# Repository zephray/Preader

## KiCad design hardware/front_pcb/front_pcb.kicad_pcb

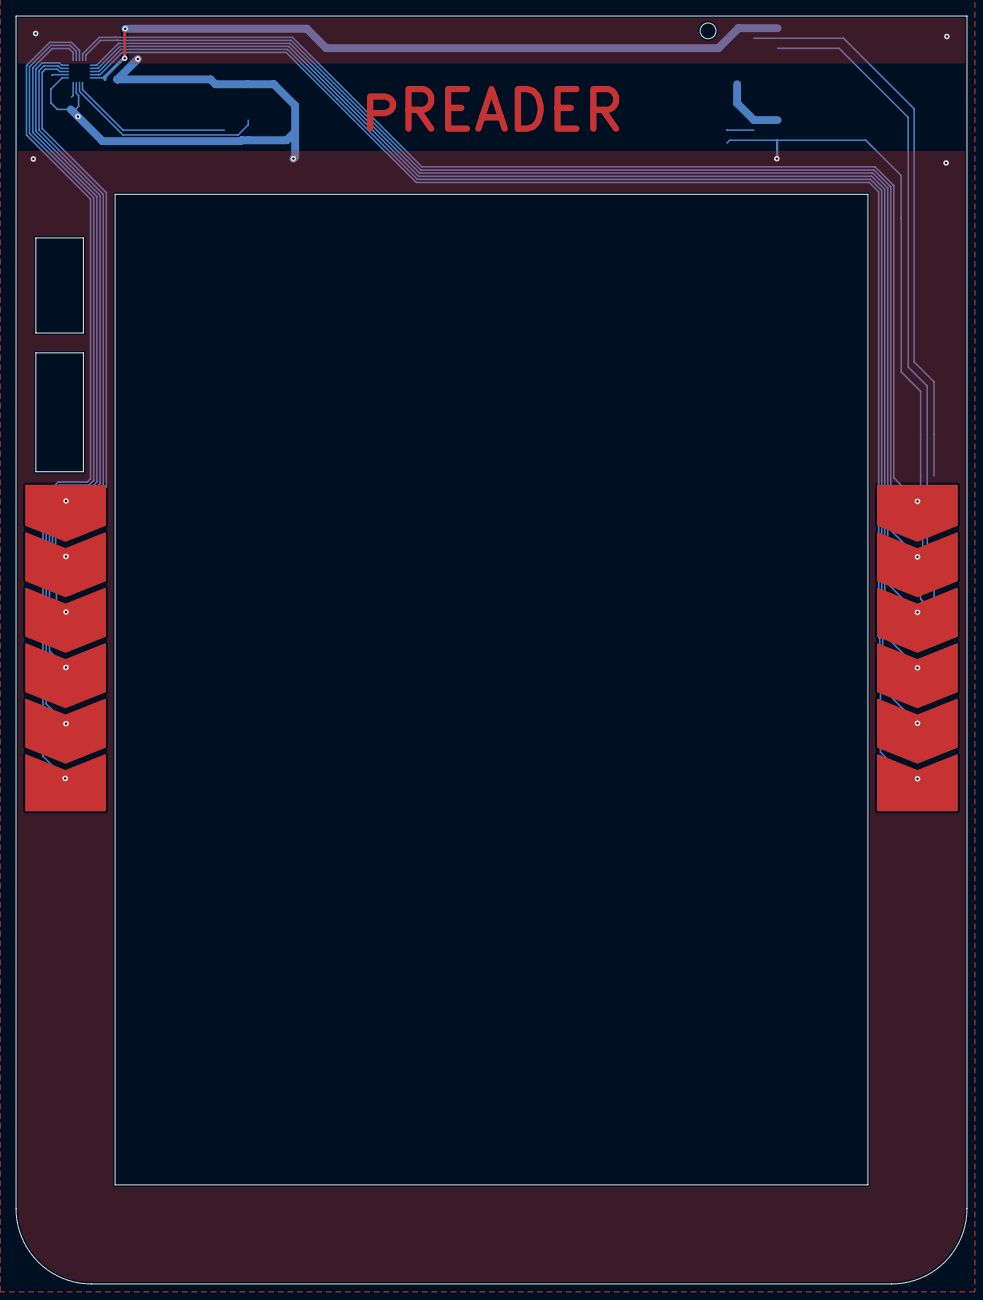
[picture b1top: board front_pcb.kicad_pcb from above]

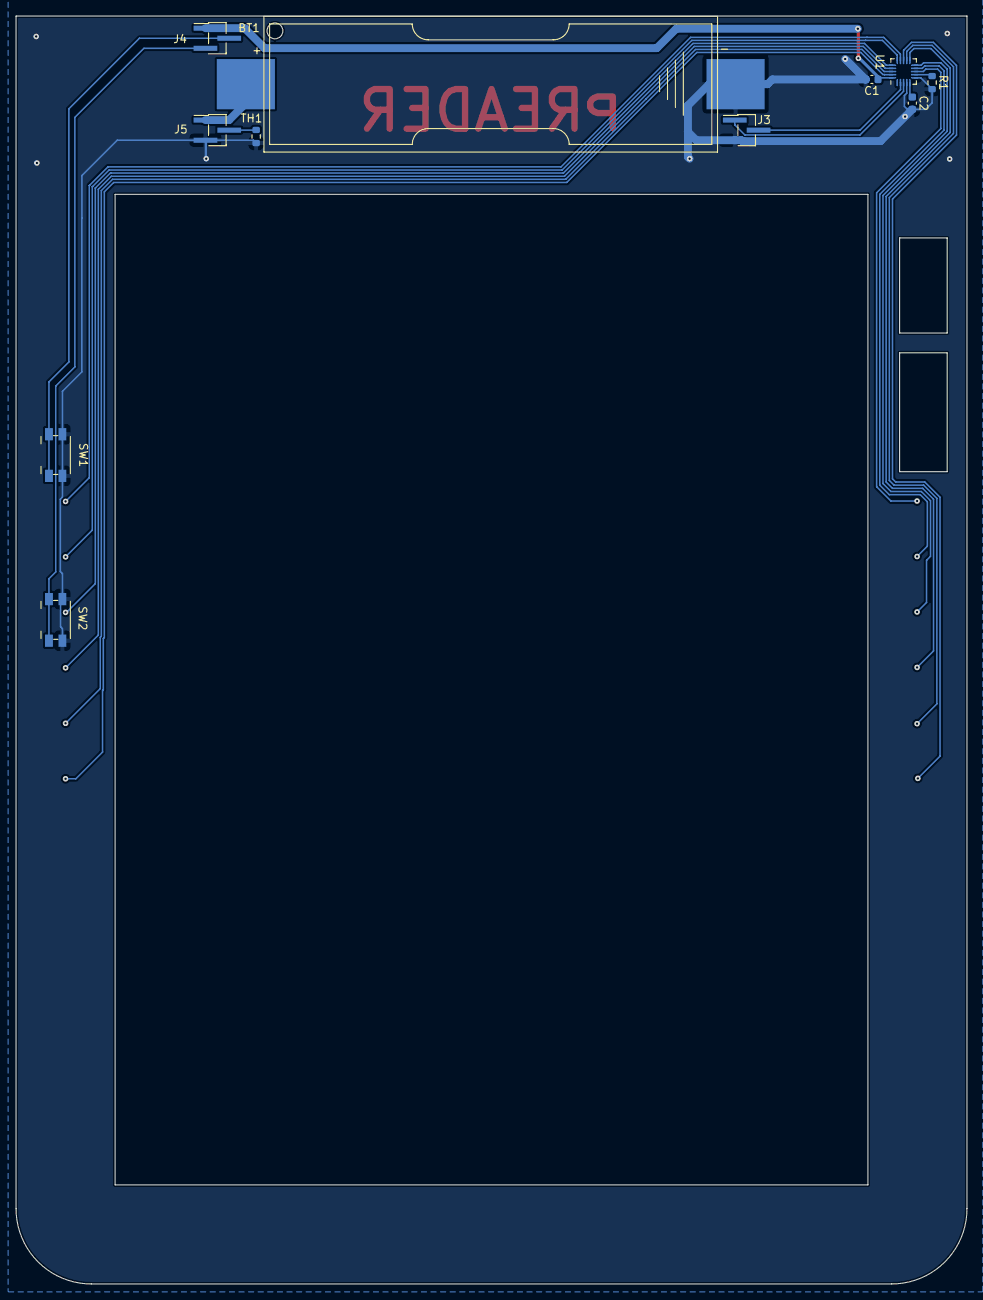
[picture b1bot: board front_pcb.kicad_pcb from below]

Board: 2 copper layers, 120.0 x 160.0 mm, 13 parts (11 on the bottom side), 22 nets.

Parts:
BT1: Keystone_1088_14800; BatteryHolder_Keystone_1088_1xAA
C1, C2: 100nF; C_0603_1608Metric
J1, J2: Conn_01x06; Touch_Sensing_6PADS
J3, J4, J5: Conn_01x03; PinHeader_1x03_P1.27mm_Vertical_SMD_Pin1Left
R1: 75K/1%; R_0603_1608Metric
SW1, SW2: EVQPUJ02K; Panasonic_EVQPUJ_EVQPUA
TH1: Thermistor_NTC; R_0603_1608Metric
U1: MPR121QR2; UQFN-20_3x3mm_P0.4mm

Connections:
+3V3: C1.1, J4.1, U1.20 (VDD)
+BATT: BT1.1 (+), J5.1
/KEY1: J4.2, SW1.1
/KEY2: J4.3, SW2.1
/KP_SCL: J3.1, U1.3 (SDA)
/KP_SDA: J3.2, U1.2 (SCL)
GND: BT1.2 (-), C1.2, C2.2, J3.3, J5.3, R1.2, SW1.2, SW2.2, TH1.2, U1.4 (ADDR), U1.6 (VSS)
unnamed: C2.1, U1.5 (VREG)
unnamed: J1.1, U1.8 (ELE0)
unnamed: J1.2, U1.9 (ELE1)
unnamed: J1.3, U1.10 (ELE2)
unnamed: J1.4, U1.11 (ELE3)
unnamed: J1.5, U1.12 (LED0/ELE4)
unnamed: J1.6, U1.13 (LED1/ELE5)
unnamed: J2.1, U1.14 (LED2/ELE6)
unnamed: J2.2, U1.15 (LED3/ELE7)
unnamed: J2.3, U1.16 (LED4/ELE8)
unnamed: J2.4, U1.17 (LED5/ELE9)
unnamed: J2.5, U1.18 (LED6/ELE10)
unnamed: J2.6, U1.19 (LED7/ELE11)
unnamed: R1.1, U1.7 (REXT)
unnamed: J5.2, TH1.1

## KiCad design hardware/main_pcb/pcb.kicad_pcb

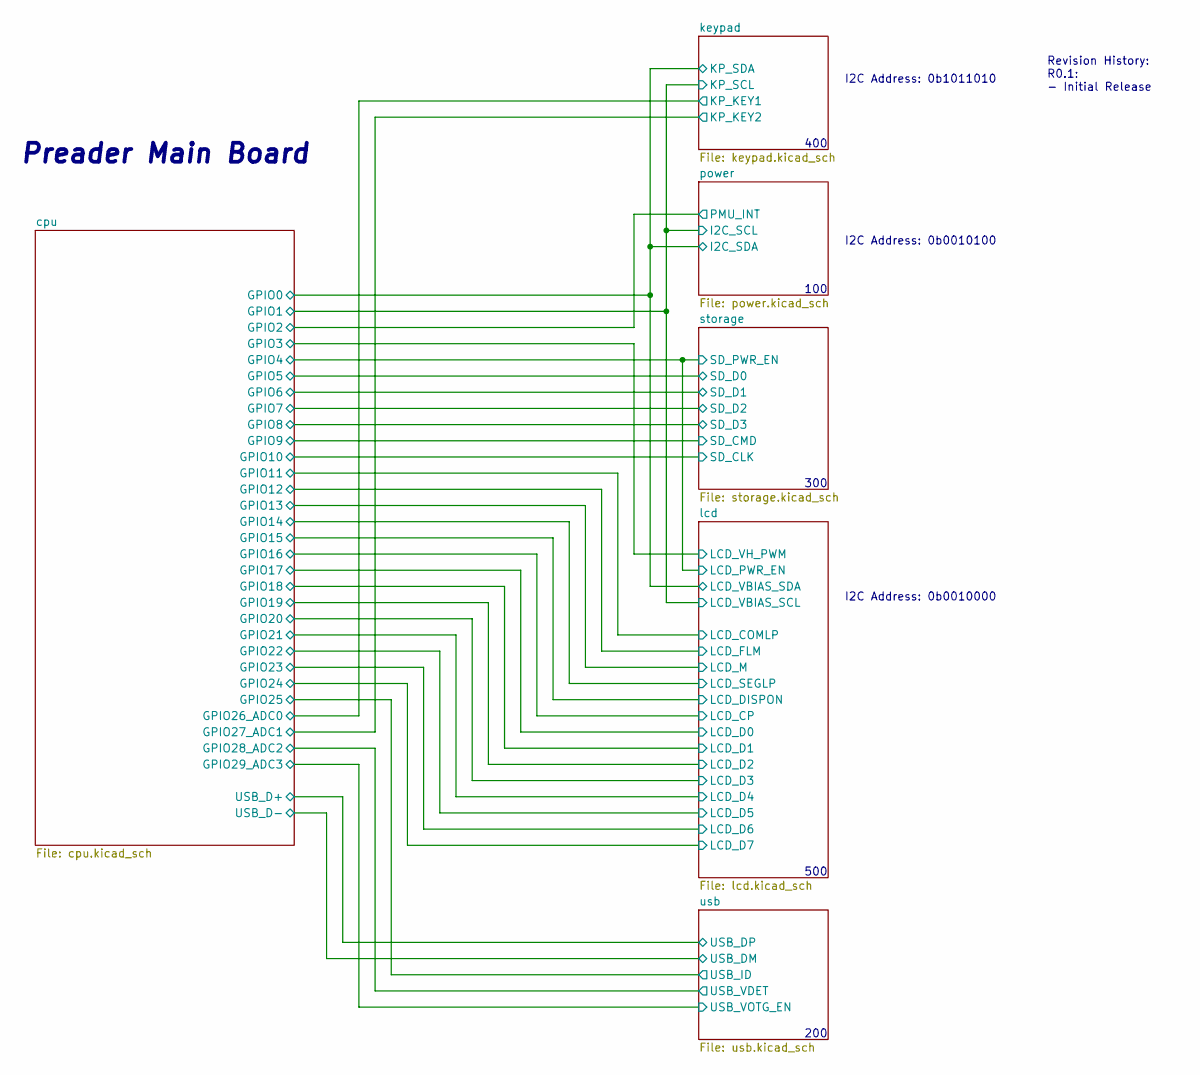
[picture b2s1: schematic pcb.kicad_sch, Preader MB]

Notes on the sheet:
Preader Main Board
400
100
300
500
200
I2C Address: 0b1011010
I2C Address: 0b0010100
I2C Address: 0b0010000
Revision History: R0.1: - Initial Release

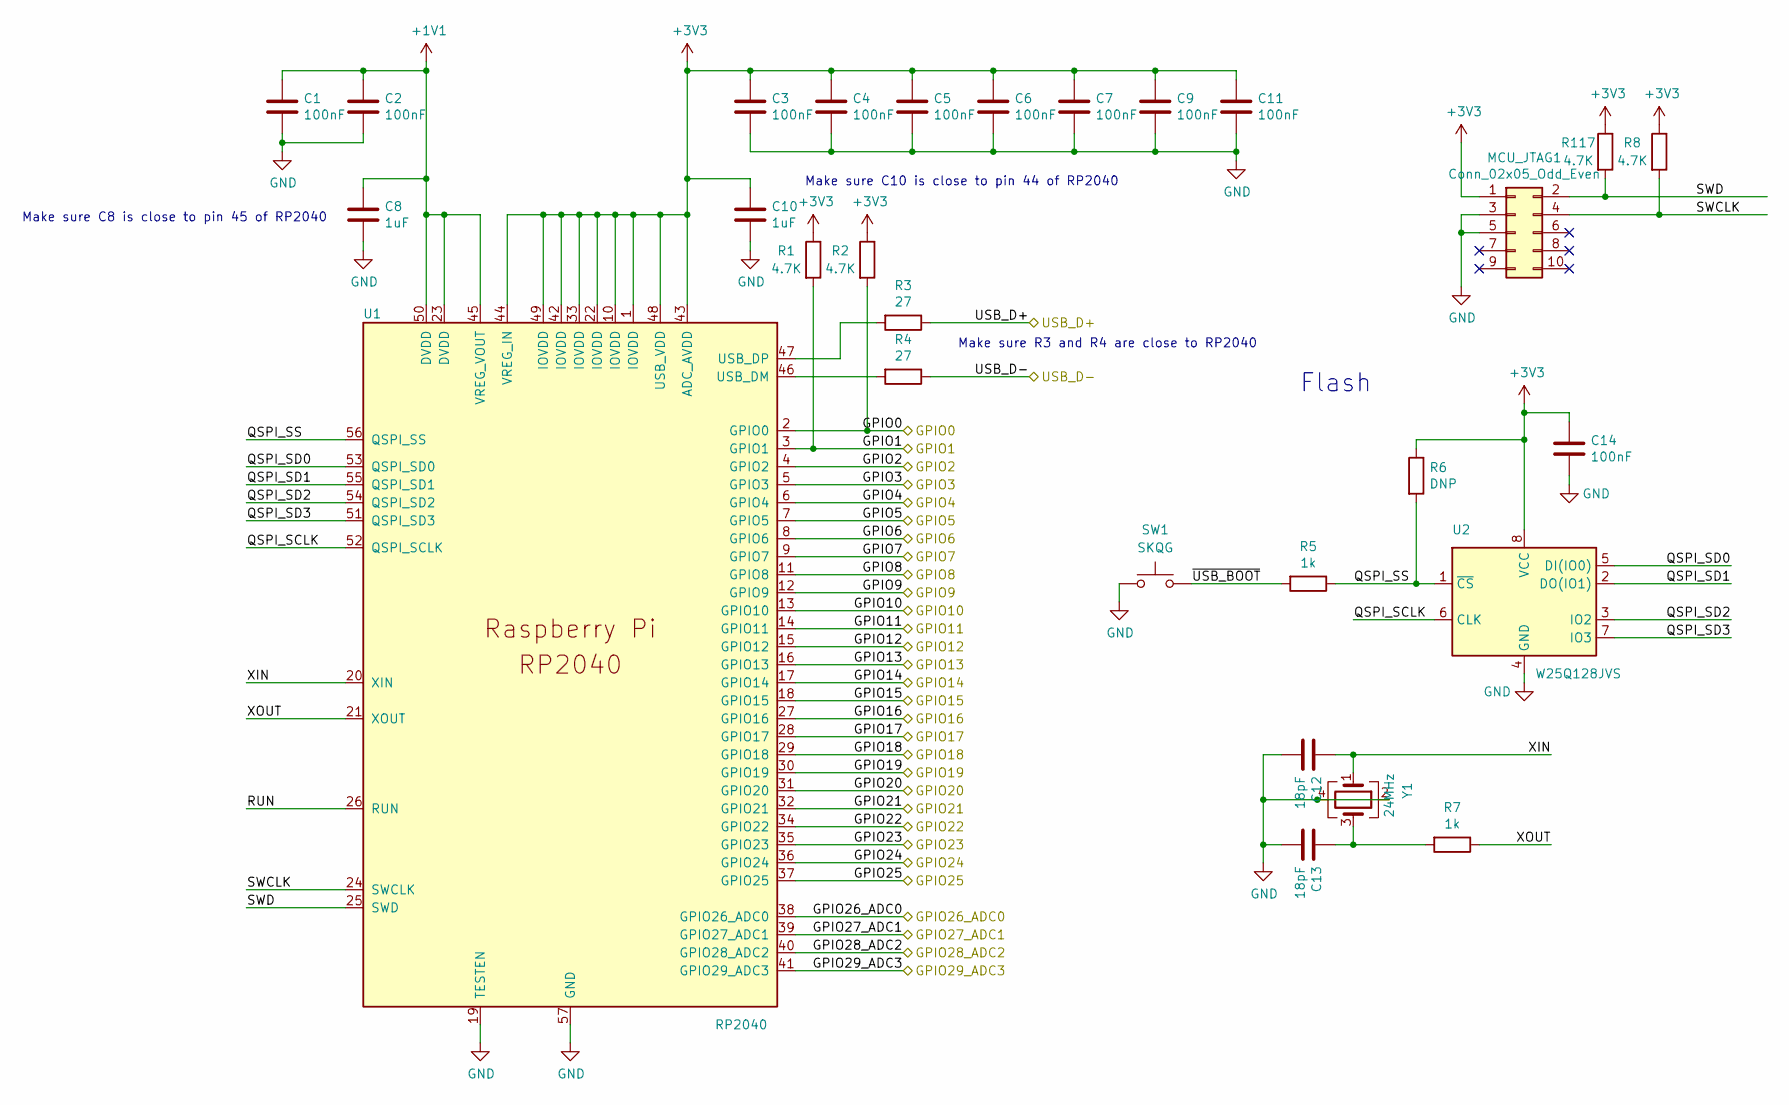
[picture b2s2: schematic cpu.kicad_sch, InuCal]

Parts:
C1, C2, C3, C4, C5, C6, C7, C9, C11, C14: 100nF; C_0402_1005Metric
C8, C10: 1uF; C_0402_1005Metric
C12, C13: 18pF; C_0402_1005Metric
MCU_JTAG1: Conn_02x05_Odd_Even; PinHeader_2x05_P1.27mm_Vertical_SMD
R1, R2, R8, R117: 4.7K; C_0402_1005Metric
R3, R4: 27; C_0402_1005Metric
R5, R7: 1k; C_0402_1005Metric
R6: DNP; C_0402_1005Metric
SW1: SKQG; SW_SPST_SKQG_WithStem
U1: RP2040; QFN-56-1EP_7x7mm_P0.4mm_EP5.6x5.6mm_ThermalVias
U2: W25Q128JVS; SOIC-8_5.23x5.23mm_P1.27mm
Y1: 24MHz; Oscillator_SMD_Abracon_ASE-4Pin_3.2x2.5mm

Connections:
+1V1: C1.1, C2.1, C8.1, U1.23 (DVDD), U1.45 (VREG_VOUT), U1.50 (DVDD)
+3V3: C3.1, C4.1, C5.1, C6.1, C7.1, C9.1, C10.1, C11.1, C14.1, MCU_JTAG1.1, R1.1, R2.1, R6.1, R8.1, R117.1, U1.1 (IOVDD), U1.10 (IOVDD), U1.22 (IOVDD), U1.33 (IOVDD), U1.42 (IOVDD), U1.43 (ADC_AVDD), U1.44 (VREG_IN), U1.48 (USB_VDD), U1.49 (IOVDD), U2.8 (VCC); also elsewhere on the board
/cpu/GPIO0: R2.2, U1.2 (GPIO0); also elsewhere on the board
/cpu/GPIO1: R1.2, U1.3 (GPIO1); also elsewhere on the board
/cpu/GPIO2: U1.4 (GPIO2); also elsewhere on the board
/cpu/GPIO3: U1.5 (GPIO3); also elsewhere on the board
/cpu/GPIO4: U1.6 (GPIO4); also elsewhere on the board
/cpu/GPIO5: U1.7 (GPIO5); also elsewhere on the board
/cpu/GPIO6: U1.8 (GPIO6); also elsewhere on the board
/cpu/GPIO7: U1.9 (GPIO7); also elsewhere on the board
/cpu/GPIO8: U1.11 (GPIO8); also elsewhere on the board
/cpu/GPIO9: U1.12 (GPIO9); also elsewhere on the board
/cpu/GPIO10: U1.13 (GPIO10); also elsewhere on the board
/cpu/GPIO11: U1.14 (GPIO11); also elsewhere on the board
/cpu/GPIO12: U1.15 (GPIO12); also elsewhere on the board
/cpu/GPIO13: U1.16 (GPIO13); also elsewhere on the board
/cpu/GPIO14: U1.17 (GPIO14); also elsewhere on the board
/cpu/GPIO15: U1.18 (GPIO15); also elsewhere on the board
/cpu/GPIO16: U1.27 (GPIO16); also elsewhere on the board
/cpu/GPIO17: U1.28 (GPIO17); also elsewhere on the board
/cpu/GPIO18: U1.29 (GPIO18); also elsewhere on the board
/cpu/GPIO19: U1.30 (GPIO19); also elsewhere on the board
/cpu/GPIO20: U1.31 (GPIO20); also elsewhere on the board
/cpu/GPIO21: U1.32 (GPIO21); also elsewhere on the board
/cpu/GPIO22: U1.34 (GPIO22); also elsewhere on the board
/cpu/GPIO23: U1.35 (GPIO23); also elsewhere on the board
/cpu/GPIO24: U1.36 (GPIO24); also elsewhere on the board
/cpu/GPIO25: U1.37 (GPIO25); also elsewhere on the board
/cpu/GPIO26_ADC0: U1.38 (GPIO26_ADC0); also elsewhere on the board
/cpu/GPIO27_ADC1: U1.39 (GPIO27_ADC1); also elsewhere on the board
/cpu/GPIO28_ADC2: U1.40 (GPIO28_ADC2); also elsewhere on the board
/cpu/GPIO29_ADC3: U1.41 (GPIO29_ADC3); also elsewhere on the board
/cpu/QSPI_SCLK: U1.52 (QSPI_SCLK), U2.6 (CLK)
/cpu/QSPI_SD0: U1.53 (QSPI_SD0), U2.5 (DI(IO0))
/cpu/QSPI_SD1: U1.55 (QSPI_SD1), U2.2 (DO(IO1))
/cpu/QSPI_SD2: U1.54 (QSPI_SD2), U2.3 (IO2)
/cpu/QSPI_SD3: U1.51 (QSPI_SD3), U2.7 (IO3)
/cpu/QSPI_SS: R5.1, R6.2, U1.56 (QSPI_SS), U2.1 (~CS)
/cpu/RUN: U1.26 (RUN)
/cpu/SWCLK: MCU_JTAG1.4, R8.2, U1.24 (SWCLK)
/cpu/SWD: MCU_JTAG1.2, R117.2, U1.25 (SWD)
/cpu/USB_D+: R3.1; also elsewhere on the board
/cpu/USB_D-: R4.1; also elsewhere on the board
/cpu/XIN: C12.1, U1.20 (XIN), Y1.1
/cpu/XOUT: R7.1, U1.21 (XOUT)
/cpu/~USB_BOOT: R5.2, SW1.2
GND: C1.2, C2.2, C3.2, C4.2, C5.2, C6.2, C7.2, C8.2, C9.2, C10.2, C11.2, C12.2, C13.2, C14.2, MCU_JTAG1.3, MCU_JTAG1.5, SW1.1, U1.19 (TESTEN), U1.57 (GND), U2.4 (GND), Y1.2, Y1.4; also elsewhere on the board
unnamed: C13.1, R7.2, Y1.3
unnamed: R3.2, U1.47 (USB_DP)
unnamed: R4.2, U1.46 (USB_DM)

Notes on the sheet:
Make sure C8 is close to pin 45 of RP2040
Make sure C10 is close to pin 44 of RP2040
Make sure R3 and R4 are close to RP2040
Flash

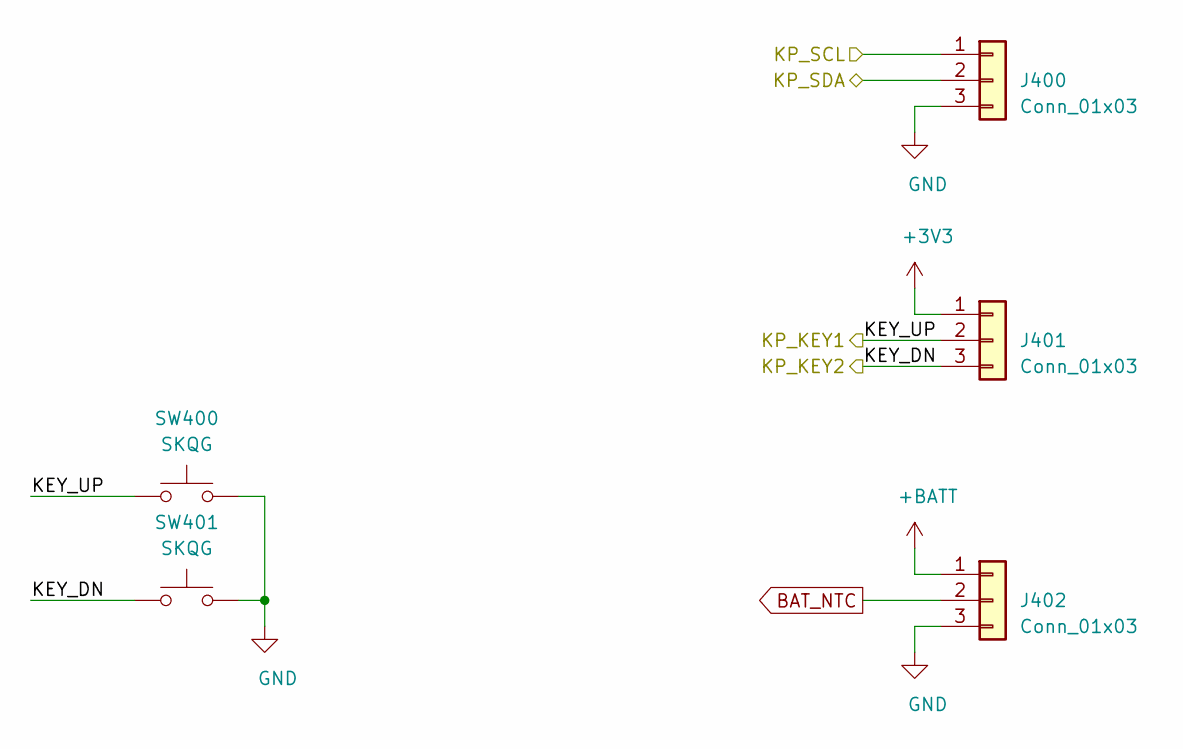
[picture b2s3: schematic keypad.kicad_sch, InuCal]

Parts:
J400, J401, J402: Conn_01x03; PinHeader_1x03_P1.27mm_Vertical
SW400, SW401: SKQG; SW_SPST_SKQG_WithStem

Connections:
+3V3: J401.1; also elsewhere on the board
+BATT: J402.1; also elsewhere on the board
/cpu/GPIO0: J400.2; also elsewhere on the board
/cpu/GPIO1: J400.1; also elsewhere on the board
/cpu/GPIO26_ADC0: J401.2, SW400.1; also elsewhere on the board
/cpu/GPIO27_ADC1: J401.3, SW401.1; also elsewhere on the board
BAT_NTC: J402.2; also elsewhere on the board
GND: J400.3, J402.3, SW400.2, SW401.2; also elsewhere on the board

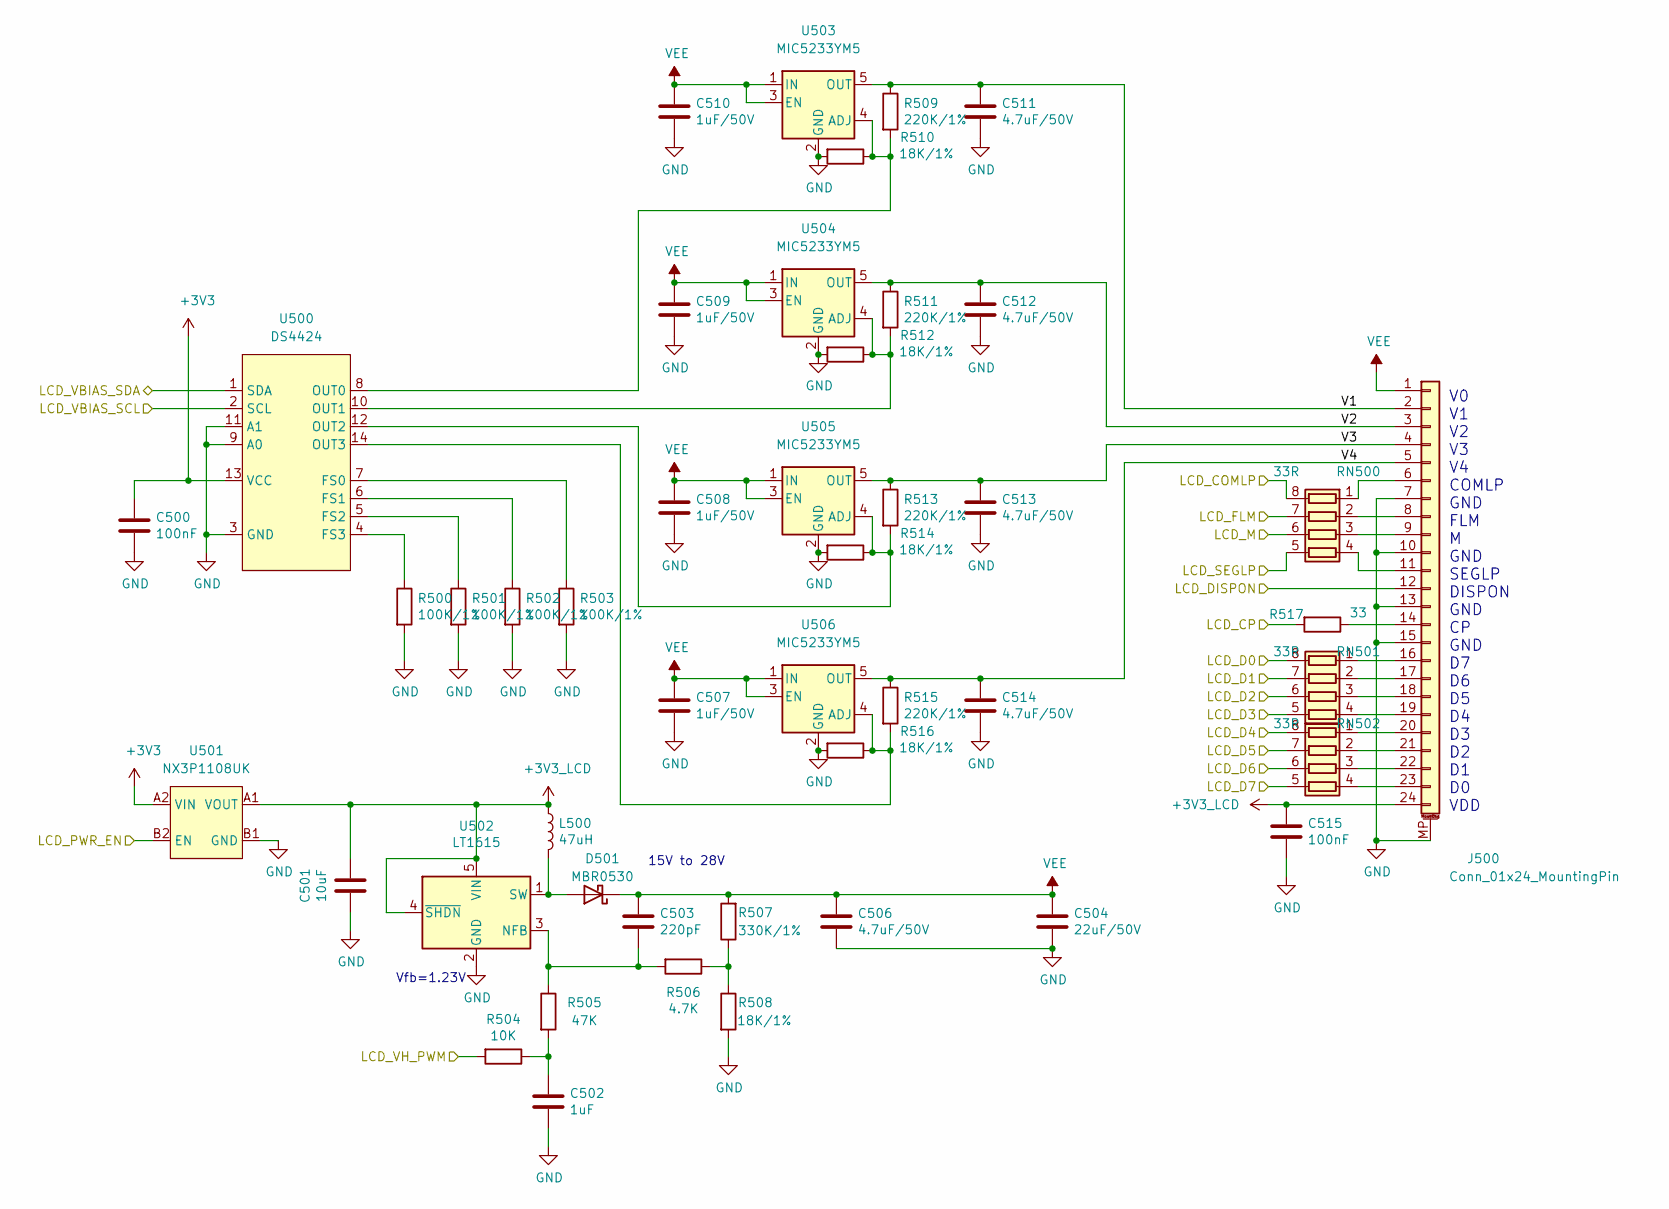
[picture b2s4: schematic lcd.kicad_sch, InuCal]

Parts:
C500, C515: 100nF; C_0402_1005Metric
C501: 10uF; C_0603_1608Metric
C502: 1uF; C_0402_1005Metric
C503: 220pF; C_0603_1608Metric
C504: 22uF/50V; C_1206_3216Metric
C506, C511, C512, C513, C514: 4.7uF/50V; C_0805_2012Metric
C507, C508, C509, C510: 1uF/50V; C_0805_2012Metric
D501: MBR0530; D_SOD-123
J500: Conn_01x24_MountingPin; Hirose_FH12-24S-0.5SH_1x24-1MP_P0.50mm_Horizontal
L500: 47uH; L_Vishay_IHLP-1212
R500, R501, R502, R503: 100K/1%; R_0402_1005Metric
R504: 10K; R_0402_1005Metric
R505: 47K; R_0402_1005Metric
R506: 4.7K; R_0402_1005Metric
R507: 330K/1%; R_0402_1005Metric
R508, R510, R512, R514, R516: 18K/1%; R_0402_1005Metric
R509, R511, R513, R515: 220K/1%; R_0402_1005Metric
R517: 33; R_0402_1005Metric
RN500, RN501, RN502: 33R; R_Array_Convex_4x0402
U500: DS4424; DFN-14-1EP_3x3mm_P0.4mm_EP1.78x2.35mm
U501: NX3P1108UK; WLCSP-4-X1-WLB0909-4_0.89x0.89mm_P0.5mm
U502: LT1615; TSOT-23-5
U503, U504, U505, U506: MIC5233YM5; SOT-23-5

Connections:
+3V3: C500.2, U500.13 (VCC), U501.A2 (VIN); also elsewhere on the board
+3V3_LCD: C501.1, C515.2, J500.24, L500.1, U501.A1 (VOUT), U502.4 (~SHDN), U502.5 (VIN)
/cpu/GPIO0: U500.1 (SDA); also elsewhere on the board
/cpu/GPIO1: U500.2 (SCL); also elsewhere on the board
/cpu/GPIO3: R504.2; also elsewhere on the board
/cpu/GPIO4: U501.B2 (EN); also elsewhere on the board
/cpu/GPIO11: RN500.8 (R1.2); also elsewhere on the board
/cpu/GPIO12: RN500.7 (R2.2); also elsewhere on the board
/cpu/GPIO13: RN500.6 (R3.2); also elsewhere on the board
/cpu/GPIO14: RN500.5 (R4.2); also elsewhere on the board
/cpu/GPIO15: J500.12; also elsewhere on the board
/cpu/GPIO16: R517.2; also elsewhere on the board
/cpu/GPIO17: RN501.8 (R1.2); also elsewhere on the board
/cpu/GPIO18: RN501.7 (R2.2); also elsewhere on the board
/cpu/GPIO19: RN501.6 (R3.2); also elsewhere on the board
/cpu/GPIO20: RN501.5 (R4.2); also elsewhere on the board
/cpu/GPIO21: RN502.8 (R1.2); also elsewhere on the board
/cpu/GPIO22: RN502.7 (R2.2); also elsewhere on the board
/cpu/GPIO23: RN502.6 (R3.2); also elsewhere on the board
/cpu/GPIO24: RN502.5 (R4.2); also elsewhere on the board
/lcd/V1: C511.2, J500.2, R509.1, U503.5 (OUT)
/lcd/V2: C512.2, J500.3, R511.1, U504.5 (OUT)
/lcd/V3: C513.2, J500.4, R513.1, U505.5 (OUT)
/lcd/V4: C514.2, J500.5, R515.1, U506.5 (OUT)
GND: C500.1, C501.2, C502.1, C504.2, C506.1, C507.1, C508.1, C509.1, C510.1, C511.1, C512.1, C513.1, C514.1, C515.1, J500.7, J500.10, J500.13, J500.15, J500.MP (MountPin), R500.2, R501.2, R502.2, R503.2, R508.2, R510.2, R512.2, R514.2, R516.2, U500.3 (GND), U500.9 (A0), U500.11 (A1), U501.B1 (GND), U502.2 (GND), U503.2 (GND), U504.2 (GND), U505.2 (GND), U506.2 (GND); also elsewhere on the board
unnamed: C502.2, R504.1, R505.2
unnamed: C503.1, R505.1, R506.2, U502.3 (NFB)
unnamed: D501.2 (A), L500.2, U502.1 (SW)
unnamed: J500.6, RN500.1 (R1.1)
unnamed: J500.8, RN500.2 (R2.1)
unnamed: J500.9, RN500.3 (R3.1)
unnamed: J500.11, RN500.4 (R4.1)
unnamed: J500.14, R517.1
unnamed: J500.16, RN501.1 (R1.1)
unnamed: J500.17, RN501.2 (R2.1)
unnamed: J500.18, RN501.3 (R3.1)
unnamed: J500.19, RN501.4 (R4.1)
unnamed: J500.20, RN502.1 (R1.1)
unnamed: J500.21, RN502.2 (R2.1)
unnamed: J500.22, RN502.3 (R3.1)
unnamed: J500.23, RN502.4 (R4.1)
unnamed: R500.1, U500.4 (FS3)
unnamed: R501.1, U500.5 (FS2)
unnamed: R502.1, U500.6 (FS1)
unnamed: R503.1, U500.7 (FS0)
unnamed: R506.1, R507.1, R508.1
unnamed: R509.2, R510.1, U500.8 (OUT0), U503.4 (ADJ)
unnamed: R511.2, R512.1, U500.10 (OUT1), U504.4 (ADJ)
unnamed: R513.2, R514.1, U500.12 (OUT2), U505.4 (ADJ)
unnamed: R515.2, R516.1, U500.14 (OUT3), U506.4 (ADJ)
VEE: C503.2, C504.1, C506.2, C507.2, C508.2, C509.2, C510.2, D501.1 (K), J500.1, R507.2, U503.1 (IN), U503.3 (EN), U504.1 (IN), U504.3 (EN), U505.1 (IN), U505.3 (EN), U506.1 (IN), U506.3 (EN)

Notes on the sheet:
Vfb=1.23V
15V to 28V
V0 V1 V2 V3 V4 COMLP GND FLM M GND SEGLP DISPON GND CP GND D7 D6 D5 D4 D3 D2 D1 D0 VDD

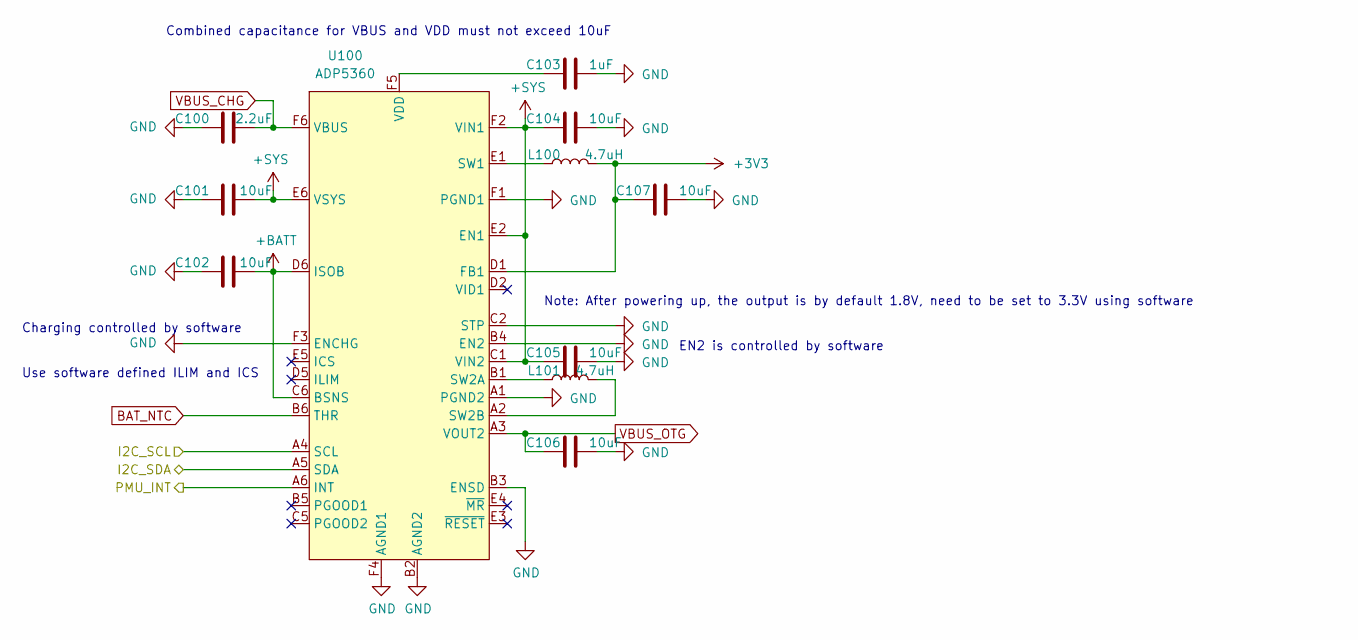
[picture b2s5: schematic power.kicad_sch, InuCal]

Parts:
C100: 2.2uF; C_0603_1608Metric
C101, C102, C104, C105, C106, C107: 10uF; C_0603_1608Metric
C103: 1uF; C_0402_1005Metric
L100, L101: 4.7uH; L_Vishay_IHLP-1212
U100: ADP5360; WLCSP-32_6x6_2.56x2.56mm

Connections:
+3V3: C107.2, L100.2, U100.D1 (FB1); also elsewhere on the board
+BATT: C102.2, U100.C6 (BSNS), U100.D6 (ISOB); also elsewhere on the board
+SYS: C101.2, C104.2, C105.2, U100.C1 (VIN2), U100.E2 (EN1), U100.E6 (VSYS), U100.F2 (VIN1)
/cpu/GPIO0: U100.A5 (SDA); also elsewhere on the board
/cpu/GPIO1: U100.A4 (SCL); also elsewhere on the board
/cpu/GPIO2: U100.A6 (INT); also elsewhere on the board
BAT_NTC: U100.B6 (THR); also elsewhere on the board
GND: C100.1, C101.1, C102.1, C103.1, C104.1, C105.1, C106.1, C107.1, U100.A1 (PGND2), U100.B2 (AGND2), U100.B3 (ENSD), U100.B4 (EN2), U100.C2 (STP), U100.F1 (PGND1), U100.F3 (ENCHG), U100.F4 (AGND1); also elsewhere on the board
unnamed: C103.2, U100.F5 (VDD)
unnamed: L100.1, U100.E1 (SW1)
unnamed: L101.1, U100.B1 (SW2A)
unnamed: L101.2, U100.A2 (SW2B)
VBUS_CHG: C100.2, U100.F6 (VBUS); also elsewhere on the board
VBUS_OTG: C106.2, U100.A3 (VOUT2); also elsewhere on the board

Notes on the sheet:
Charging controlled by software
Use software defined ILIM and ICS
Combined capacitance for VBUS and VDD must not exceed 10uF
Note: After powering up, the output is by default 1.8V, need to be set to 3.3V using software
EN2 is controlled by software

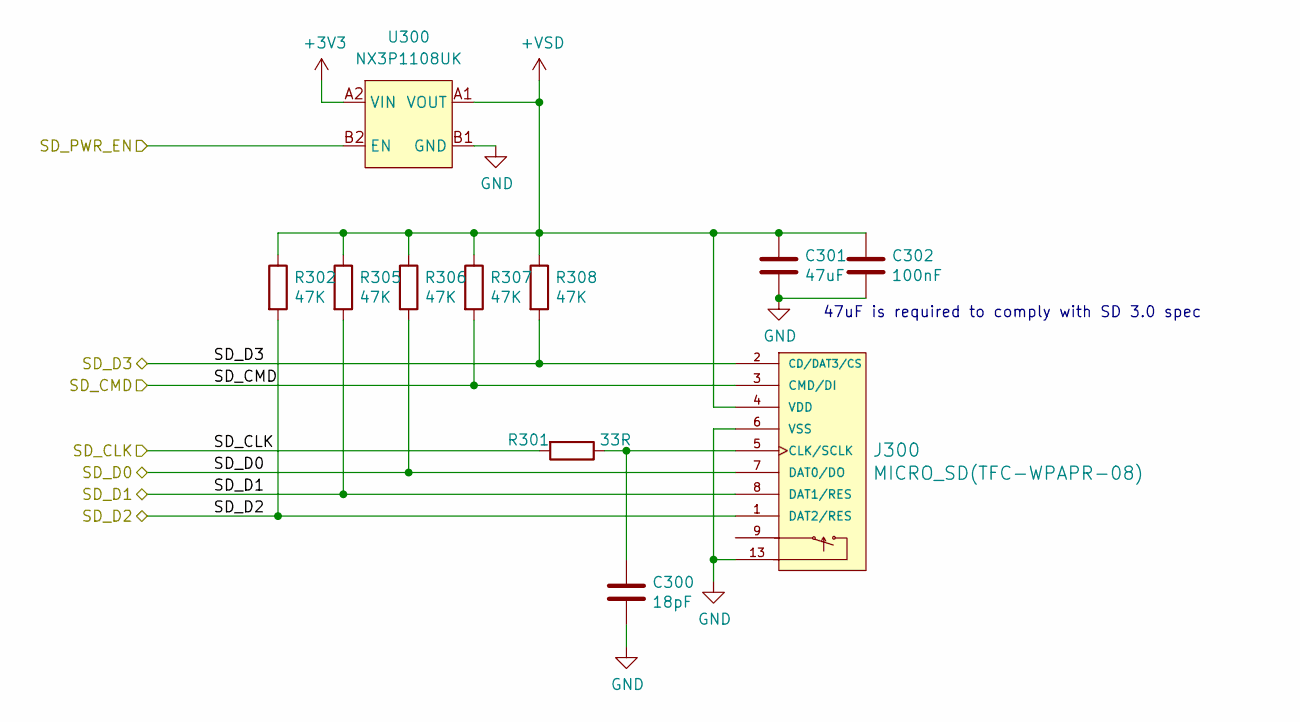
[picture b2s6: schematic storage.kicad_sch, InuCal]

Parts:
C300: 18pF; C_0402_1005Metric
C301: 47uF; C_0805_2012Metric
C302: 100nF; C_0402_1005Metric
J300: MICRO_SD(TFC-WPAPR-08); TFC-WPAPR-08
R301: 33R; R_0402_1005Metric
R302, R305, R306, R307, R308: 47K; R_0402_1005Metric
U300: NX3P1108UK; WLCSP-4-X1-WLB0909-4_0.89x0.89mm_P0.5mm

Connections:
+3V3: U300.A2 (VIN); also elsewhere on the board
+VSD: C301.1, C302.1, J300.4 (VDD), R302.1, R305.1, R306.1, R307.1, R308.1, U300.A1 (VOUT)
/cpu/GPIO4: U300.B2 (EN); also elsewhere on the board
/cpu/GPIO5: J300.7 (DAT0/DO), R306.2; also elsewhere on the board
/cpu/GPIO6: J300.8 (DAT1/RES), R305.2; also elsewhere on the board
/cpu/GPIO7: J300.1 (DAT2/RES), R302.2; also elsewhere on the board
/cpu/GPIO8: J300.2 (CD/DAT3/CS), R308.2; also elsewhere on the board
/cpu/GPIO9: J300.3 (CMD/DI), R307.2; also elsewhere on the board
/cpu/GPIO10: R301.2; also elsewhere on the board
GND: C300.2, C301.2, C302.2, J300.6 (VSS), J300.10, J300.11, J300.12, J300.13, U300.B1 (GND); also elsewhere on the board
unnamed: C300.1, J300.5 (CLK/SCLK), R301.1

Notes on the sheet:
47uF is required to comply with SD 3.0 spec

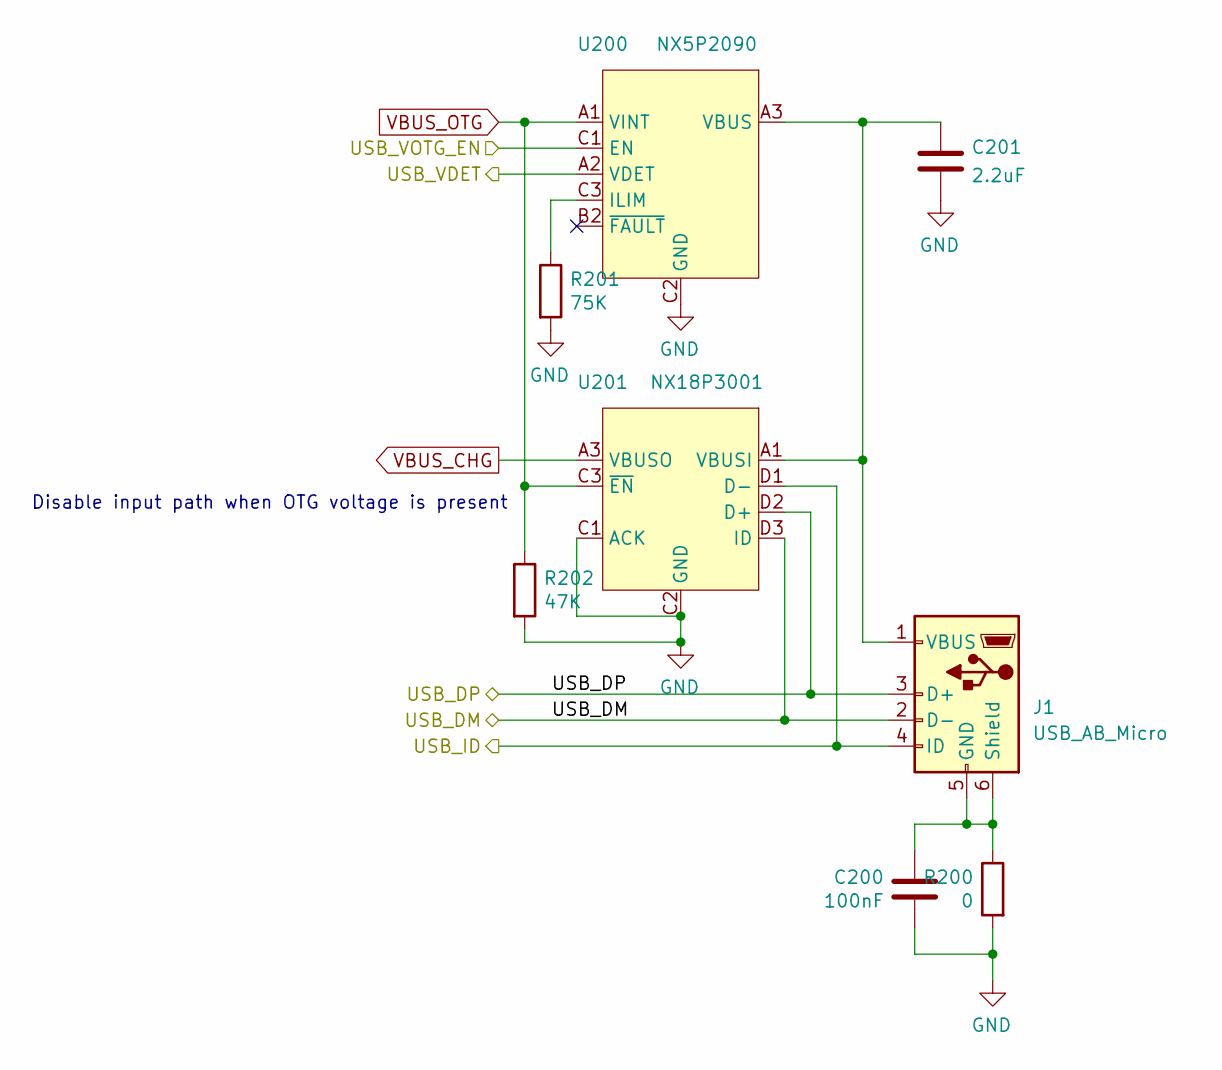
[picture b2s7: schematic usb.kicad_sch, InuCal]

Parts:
C200: 100nF; C_0805_2012Metric
C201: 2.2uF; C_0603_1608Metric
J1: USB_AB_Micro; USB_Micro-AB_Molex_47590-0001
R200: 0; R_0805_2012Metric
R201: 75K; R_0402_1005Metric
R202: 47K; R_0402_1005Metric
U200: NX5P2090; WLCSP-9_3x3_1.36x1.36mm
U201: NX18P3001; WLCSP-12_3x4_1.36x1.66mm

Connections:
/cpu/GPIO25: J1.4 (ID), U201.D1 (D-); also elsewhere on the board
/cpu/GPIO28_ADC2: U200.A2 (VDET); also elsewhere on the board
/cpu/GPIO29_ADC3: U200.C1 (EN); also elsewhere on the board
/cpu/USB_D+: J1.3 (D+), U201.D2 (D+); also elsewhere on the board
/cpu/USB_D-: J1.2 (D-), U201.D3 (ID); also elsewhere on the board
GND: C200.2, C201.1, R200.2, R201.2, R202.2, U200.C2 (GND), U201.C1 (ACK), U201.C2 (GND); also elsewhere on the board
unnamed: C200.1, J1.5 (GND), J1.6 (Shield), R200.1
unnamed: C201.2, J1.1 (VBUS), U200.A3 (VBUS), U200.B3 (VBUS), U201.A1 (VBUSI), U201.A2 (VBUSI), U201.B1 (VBUSI)
unnamed: R201.1, U200.C3 (ILIM)
VBUS_CHG: U201.A3 (VBUSO), U201.B2 (VBUSO), U201.B3 (VBUSO); also elsewhere on the board
VBUS_OTG: R202.1, U200.A1 (VINT), U200.B1 (VINT), U201.C3 (~EN); also elsewhere on the board

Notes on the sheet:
Disable input path when OTG voltage is present

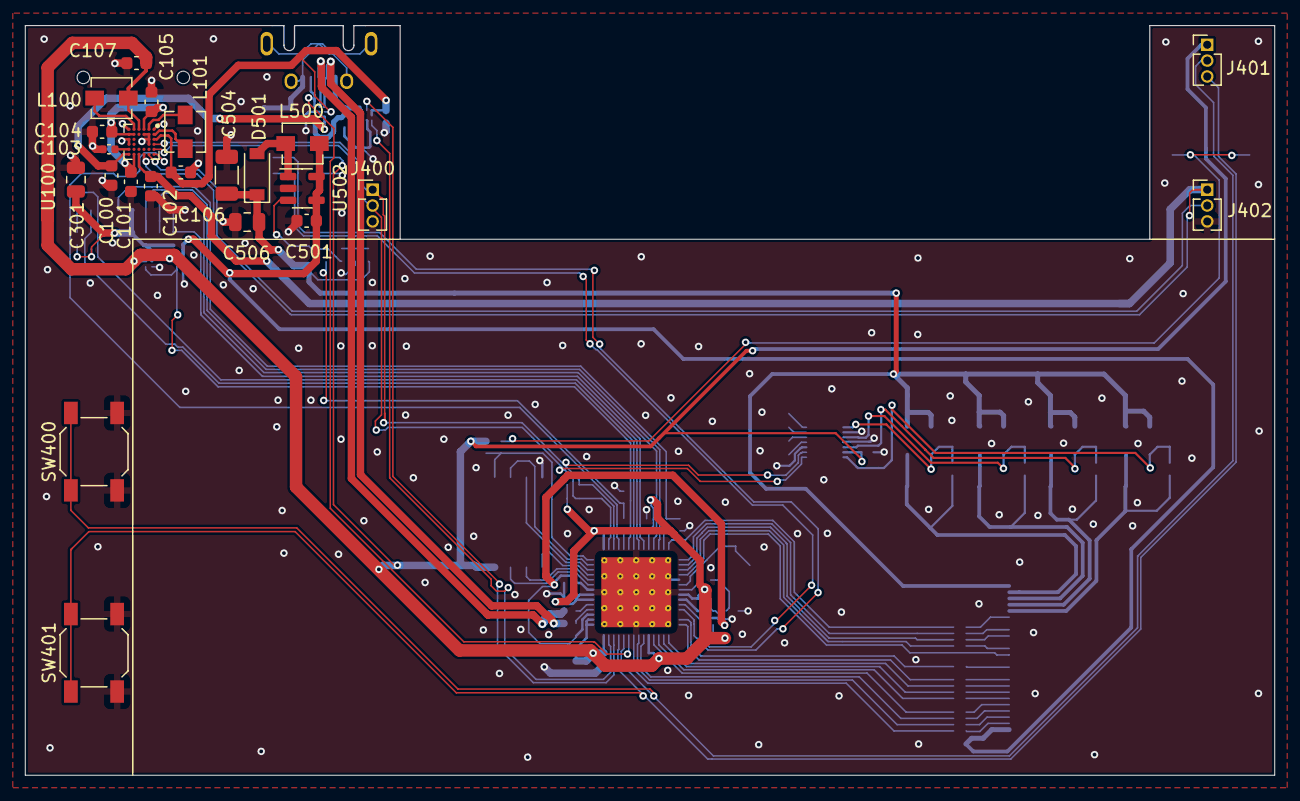
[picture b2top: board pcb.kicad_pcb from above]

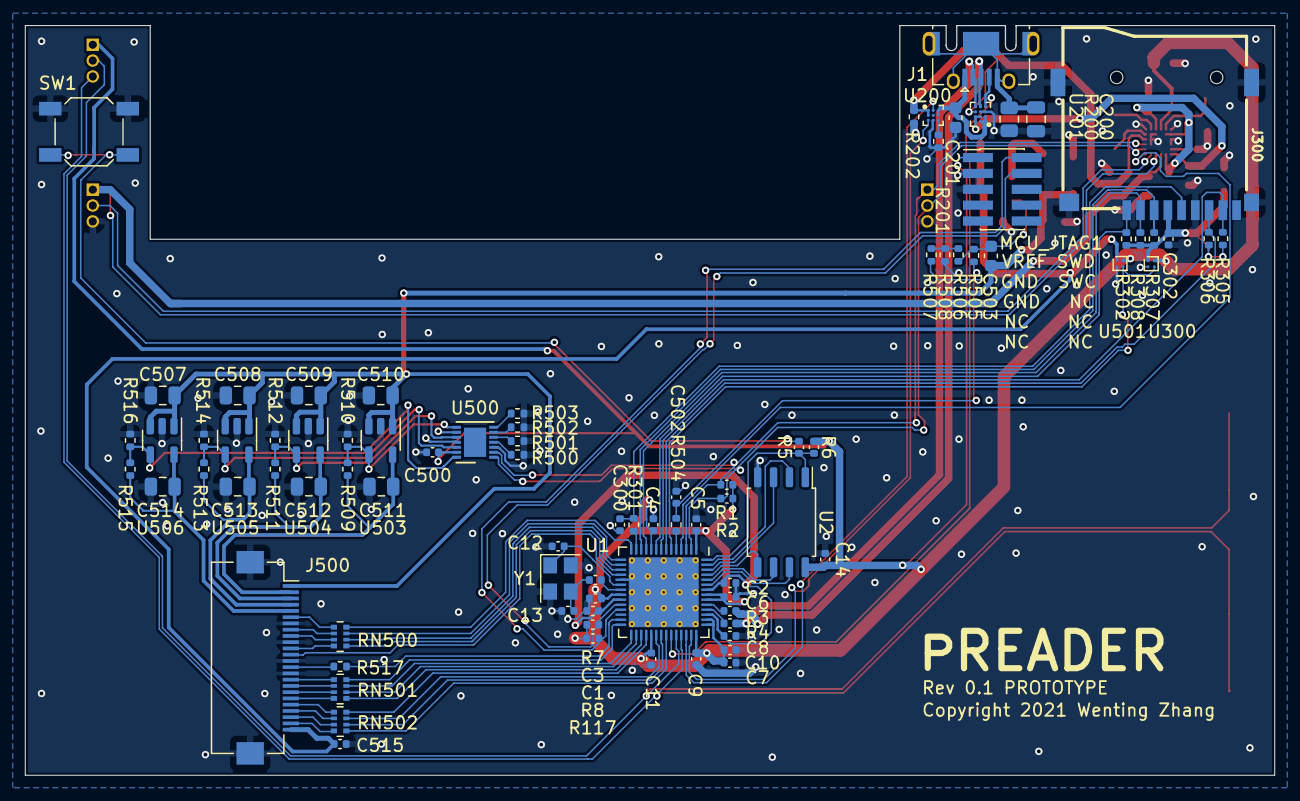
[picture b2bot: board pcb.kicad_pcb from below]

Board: 2 copper layers, 100.0 x 60.0 mm, 109 parts (86 on the bottom side), 94 nets.

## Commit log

2021-02-02 - Add license
2021-02-02 - R0P1 schematic draft
2021-02-02 - Rename pcb to main_pcb
2021-02-05 - Initial PCB layout
2021-02-07 - PCB rev 0p1 draft
2021-02-08 - harware rev 0.1 freeze
2021-04-16 fw: initial bring-up

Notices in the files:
hardware/main_pcb/pcb.kicad_pcb:
Copyright 2021 Wenting Zhang
